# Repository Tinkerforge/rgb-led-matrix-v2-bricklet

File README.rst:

RGB LED Matrix Bricklet 2.0
====================

**This Bricklet is currently in development.**

This repository contains the firmware source code and the hardware design
files. The documentation generator configs can be found at
https://github.com/Tinkerforge/generators

Repository Content
------------------

software/:
 * examples/: Examples for all supported languages
 * build/: Compiled files
 * src/: Source code of firmware
 * Makefile: Makefile to build project

hardware/:
 * Contains KiCad project files and additionally schematics as PDF

datasheets/:
 * Contains datasheets for sensors and complex ICs that are used

Hardware
--------

The hardware is designed with the open source EDA Suite KiCad
(http://www.kicad.org). Before you are able to open the files,
you have to install the Tinkerforge kicad-libraries
(https://github.com/Tinkerforge/kicad-libraries). You can either clone
them directly in hardware/ or clone them in a separate folder and
symlink them into hardware/
(ln -s kicad_path/kicad-libraries project_path/hardware). After that you
can open the .pro file in hardware/ with KiCad and from there view and
modify the schematics and the PCB layout.

Software
--------

If you want to do your own Brick/Bricklet firmware development we highly
recommend that you use our build environment setup script and read the
tutorial (https://www.tinkerforge.com/en/doc/Tutorials/Tutorial_Build_Environment/Tutorial.html).

To compile the C code we recommend you to install the newest GNU Arm Embedded
Toolchain (https://launchpad.net/gcc-arm-embedded/+download).
You also need to install bricklib2 (https://github.com/Tinkerforge/bricklib2).

You can either clone it directly in software/src/ or clone it in a
separate folder and symlink it into software/src/
(ln -s bricklib_path/bricklib2 project_path/software/src/). Finally make sure to
have CMake installed (http://www.cmake.org/cmake/resources/software.html).

After that you can build the firmware by invoking make in software/.
The firmware (.zbin) can then be found in software/build/ and uploaded
with brickv (click button "Flashing" on start screen).

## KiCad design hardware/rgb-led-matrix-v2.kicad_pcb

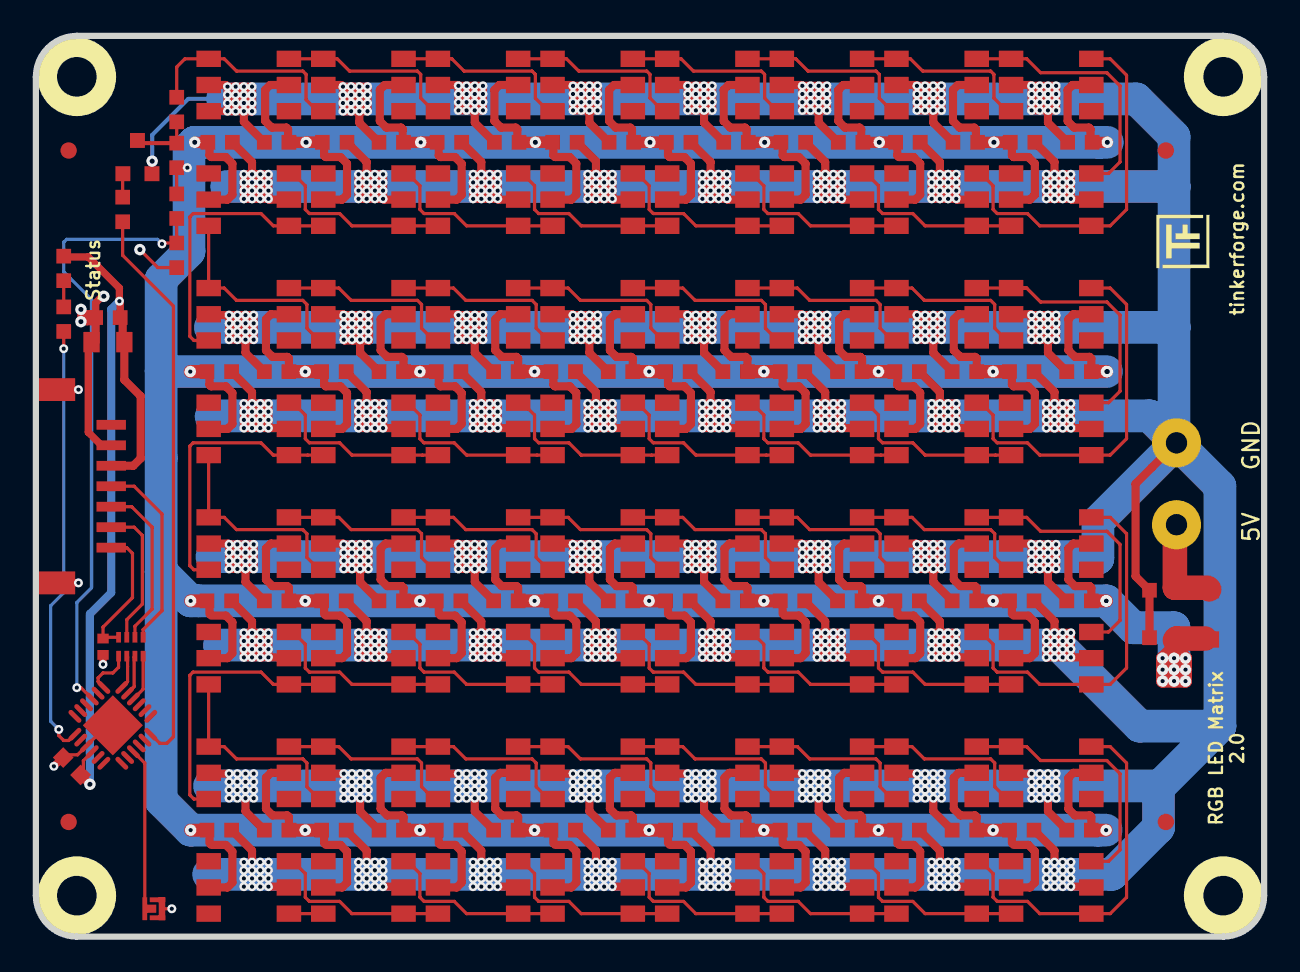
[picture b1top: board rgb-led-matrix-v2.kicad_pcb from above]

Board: 2 copper layers, 75.0 x 55.0 mm, 158 parts (0 on the bottom side), 83 nets.

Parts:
C1, C6, C7, C8, C9, C10, C11, C12, C13, C14, C15, C16, C17, C18, C19, C20, C21, C22, C23, C24, C25, C26, C27, C28, C29, C30, C31, C32, C33, C34, C35, C36, C37, C38, C39, C40, C41, C42, C43, C44, C45, C46, C47, C48, C49, C50, C51, C52, C53, C54, C55, C56, C57, C58, C59, C60, C61, C62, C63, C64, C65, C66, C67, C68, C69: 100nF; C0603F
C2, C4, C5: 1uF; C0603F
C3: 10uF; C0805
C70: 220pF; C0402F
D1: LED blue; D0603F
FB2: FB 6A; R1206
Fiducial_Mark: VAL**; Fiducial_Mark
Fiducial_Mark#2, Fiducial_Mark#3, Fiducial_Mark#4: VAL**; Fiducial_Mark
J1: AKL_5_2
P1: CONN_01X02; SolderJumper
P2: CON-SENSOR; CON-SENSOR2
Q1: 2N7002P; SOT23GDS
R1, R2, R5, R6: 1k; R0603F
R3: 100; R0603F
R4: 330; R0603F
RP1: 82; 4X0402
U1: XMC1100-16; QFN24-4x4mm-0.5mm
U2, U3, U4, U5: DRILL; DRILL_NP
U6, U7, U8, U9, U10, U11, U12, U13, U14, U15, U16, U17, U18, U19, U20, U21, U22, U23, U24, U25, U26, U27, U28, U29, U30, U31, U32, U33, U34, U35, U36, U37, U38, U39, U40, U41, U42, U43, U44, U45, U46, U47, U48, U49, U50, U51, U52, U53, U54, U55, U56, U57, U58, U59, U60, U61, U62, U63, U64, U65, U66, U67, U68, U69: WS2813B
VAL: WEEE_7mm
VAL#2: CE_5mm

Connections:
3V3: C1.2, C2.2, C3.2, D1.1, P2.3, U1.10
GND: C1.1, C2.1, C3.1, C4.1, C5.1, C6.1, C7.1, C8.1, C9.1, C10.1, C11.1, C12.1, C13.1, C14.1, C15.1, C16.1, C17.1, C18.1, C19.1, C20.1, C21.1, C22.1, C23.1, C24.1, C25.1, C26.1, C27.1, C28.1, C29.1, C30.1, C31.1, C32.1, C33.1, C34.1, C35.1, C36.1, C37.1, C38.1, C39.1, C40.1, C41.1, C42.1, C43.1, C44.1, C45.1, C46.1, C47.1, C48.1, C49.1, C50.1, C51.1, C52.1, C53.1, C54.1, C55.1, C56.1, C57.1, C58.1, C59.1, C60.1, C61.1, C62.1, C63.1, C64.1, C65.1, C66.1, C67.1, C68.1, C69.1, C70.1, J1.1, P1.1, P2.2, P2.EP, Q1.S, R6.2, U1.9, U1.EXP, U6.5, U6.6, U7.5, U8.5, U9.5, U10.5, U11.5, U12.5, U13.5, U14.5, U15.5, U16.5, U17.5, U18.5, U19.5, U20.5, U21.5, U22.5, U23.5, U24.5, U25.5, U26.5, U27.5, U28.5, U29.5, U30.5, U31.5, U32.5, U33.5, U34.5, U35.5, U36.5, U37.5, U38.5, U39.5, U40.5, U41.5, U42.5, U43.5, U44.5, U45.5, U46.5, U47.5, U48.5, U49.5, U50.5, U51.5, U52.5, U53.5, U54.5, U55.5, U56.5, U57.5, U58.5, U59.5, U60.5, U61.5, U62.5, U63.5, U64.5, U65.5, U66.5, U67.5, U68.5, U69.5
unnamed: C5.2, FB2.1, J1.2
unnamed: C70.2, P2.7, RP1.4
unnamed: D1.2, R1.1
unnamed: P1.2, U1.15
unnamed: P2.4, RP1.1
unnamed: P2.5, RP1.2
unnamed: P2.6, RP1.3
unnamed: Q1.D, R2.1, R4.2
unnamed: Q1.G, R3.1
unnamed: R1.2, U1.7
unnamed: R3.2, U1.18
unnamed: R4.1, U6.4, U11.6
unnamed: U10.3, U15.4, U20.6
unnamed: U10.4, U15.6, U69.3
unnamed: U10.6, U64.3, U69.4
unnamed: U11.3, U16.4, U21.6
unnamed: U6.3, U11.4, U16.6
unnamed: U12.3, U17.4, U22.6
unnamed: U7.3, U12.4, U17.6
unnamed: U7.4, U12.6, U66.3
unnamed: U13.3, U18.4, U23.6
unnamed: U8.3, U13.4, U18.6
unnamed: U8.4, U13.6, U67.3
unnamed: U14.3, U19.4, U24.6
unnamed: U9.3, U14.4, U19.6
unnamed: U9.4, U14.6, U68.3
unnamed: U15.3, U20.4, U25.6
unnamed: U16.3, U21.4, U26.6
unnamed: U17.3, U22.4, U27.6
unnamed: U18.3, U23.4, U28.6
unnamed: U19.3, U24.4, U29.6
unnamed: U20.3, U25.4, U30.6
unnamed: U21.3, U26.4, U31.6
unnamed: U22.3, U27.4, U32.6
unnamed: U23.3, U28.4, U33.6
unnamed: U24.3, U29.4, U34.6
unnamed: U25.3, U30.4, U35.6
unnamed: U26.3, U31.4, U36.6
unnamed: U27.3, U32.4, U37.6
unnamed: U28.3, U33.4, U38.6
unnamed: U29.3, U34.4, U39.6
unnamed: U30.3, U35.4, U40.6
unnamed: U31.3, U36.4, U41.6
unnamed: U32.3, U37.4, U42.6
unnamed: U33.3, U38.4, U43.6
unnamed: U34.3, U39.4, U44.6
unnamed: U35.3, U40.4, U45.6
unnamed: U36.3, U41.4, U46.6
unnamed: U37.3, U42.4, U47.6
unnamed: U38.3, U43.4, U48.6
unnamed: U39.3, U44.4, U49.6
unnamed: U40.3, U45.4, U50.6
unnamed: U41.3, U46.4, U51.6
unnamed: U42.3, U47.4, U52.6
unnamed: U43.3, U48.4, U53.6
unnamed: U44.3, U49.4, U54.6
unnamed: U45.3, U50.4, U55.6
unnamed: U46.3, U51.4, U56.6
unnamed: U47.3, U52.4, U57.6
unnamed: U48.3, U53.4, U58.6
unnamed: U49.3, U54.4, U59.6
unnamed: U50.3, U55.4, U60.6
unnamed: U51.3, U56.4, U61.6
unnamed: U52.3, U57.4, U62.6
unnamed: U53.3, U58.4, U63.6
unnamed: U54.3, U59.4, U64.6
unnamed: U55.3, U60.4, U65.6
unnamed: U56.3, U61.4, U66.6
unnamed: U57.3, U62.4, U67.6
unnamed: U58.3, U63.4, U68.6
unnamed: U59.3, U64.4, U69.6
unnamed: U60.3, U65.4
unnamed: U7.6, U61.3, U66.4
unnamed: U8.6, U62.3, U67.4
unnamed: U9.6, U63.3, U68.4
S-CLK: RP1.7, U1.23
S-CS: RP1.8, U1.22
S-MISO: RP1.5, U1.1
S-MOSI: RP1.6, U1.24
VCC: C4.2, C6.2, C7.2, C8.2, C9.2, C10.2, C11.2, C12.2, C13.2, C14.2, C15.2, C16.2, C17.2, C18.2, C19.2, C20.2, C21.2, C22.2, C23.2, C24.2, C25.2, C26.2, C27.2, C28.2, C29.2, C30.2, C31.2, C32.2, C33.2, C34.2, C35.2, C36.2, C37.2, C38.2, C39.2, C40.2, C41.2, C42.2, C43.2, C44.2, C45.2, C46.2, C47.2, C48.2, C49.2, C50.2, C51.2, C52.2, C53.2, C54.2, C55.2, C56.2, C57.2, C58.2, C59.2, C60.2, C61.2, C62.2, C63.2, C64.2, C65.2, C66.2, C67.2, C68.2, C69.2, FB2.2, R2.2, R5.1, U6.2, U7.2, U8.2, U9.2, U10.2, U11.2, U12.2, U13.2, U14.2, U15.2, U16.2, U17.2, U18.2, U19.2, U20.2, U21.2, U22.2, U23.2, U24.2, U25.2, U26.2, U27.2, U28.2, U29.2, U30.2, U31.2, U32.2, U33.2, U34.2, U35.2, U36.2, U37.2, U38.2, U39.2, U40.2, U41.2, U42.2, U43.2, U44.2, U45.2, U46.2, U47.2, U48.2, U49.2, U50.2, U51.2, U52.2, U53.2, U54.2, U55.2, U56.2, U57.2, U58.2, U59.2, U60.2, U61.2, U62.2, U63.2, U64.2, U65.2, U66.2, U67.2, U68.2, U69.2
VIN: R5.2, R6.1, U1.3

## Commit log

2019-02-04 add readme
2019-02-04 added kicad project files
2019-02-04 changed schematic ws2813b led
2019-02-04 updated pcb layout for ws2813b led
2019-02-05 routing powerlanes on backside
2019-02-05 changed pcb layout
2019-02-05 final pcb design
2019-02-05 added ws2813b datasheet
2019-02-05 corrected Fab.Layer
2019-02-05 pcb design
2019-02-05 ordered data
2019-02-06 added .gitignore
2021-10-25 Update KiCad link
    https://www.kicad.org/blog/2021/10/Avoid-links-to-former-kicad-domain/
2022-07-06 Add license files.

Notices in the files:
hardware/rgb-led-matrix-v2.kicad_pcb:
Licensed under CERN OHL v.1.1
Copyright (©) 2019, T.Schneidermann
Copyright Tinkerforge GmbH 2017.
This documentation describes Open Hardware and is licensed under the
CERN OHL v. 1.1.
